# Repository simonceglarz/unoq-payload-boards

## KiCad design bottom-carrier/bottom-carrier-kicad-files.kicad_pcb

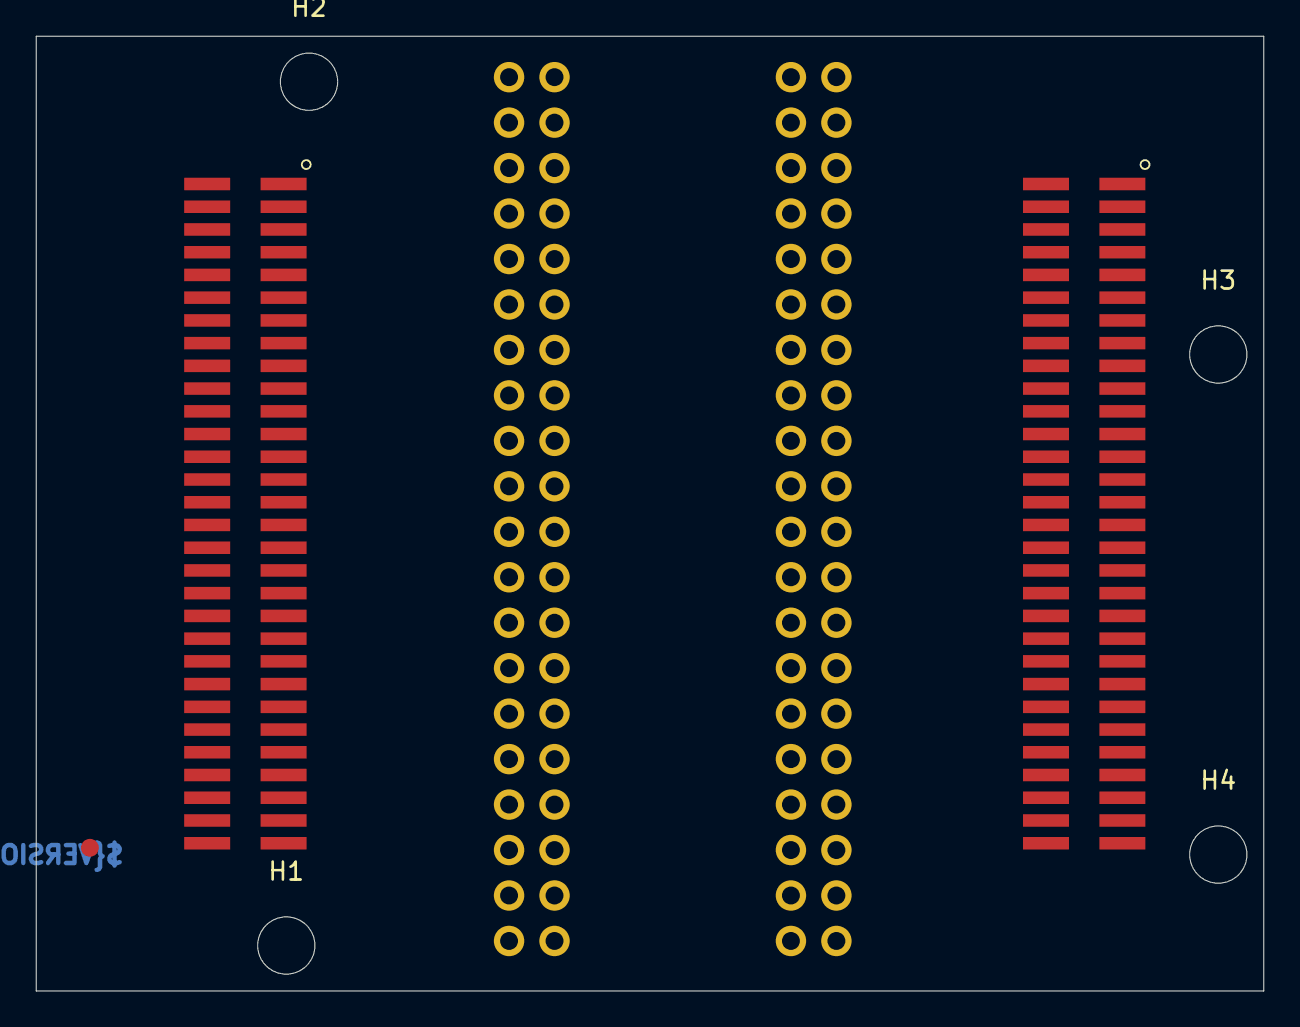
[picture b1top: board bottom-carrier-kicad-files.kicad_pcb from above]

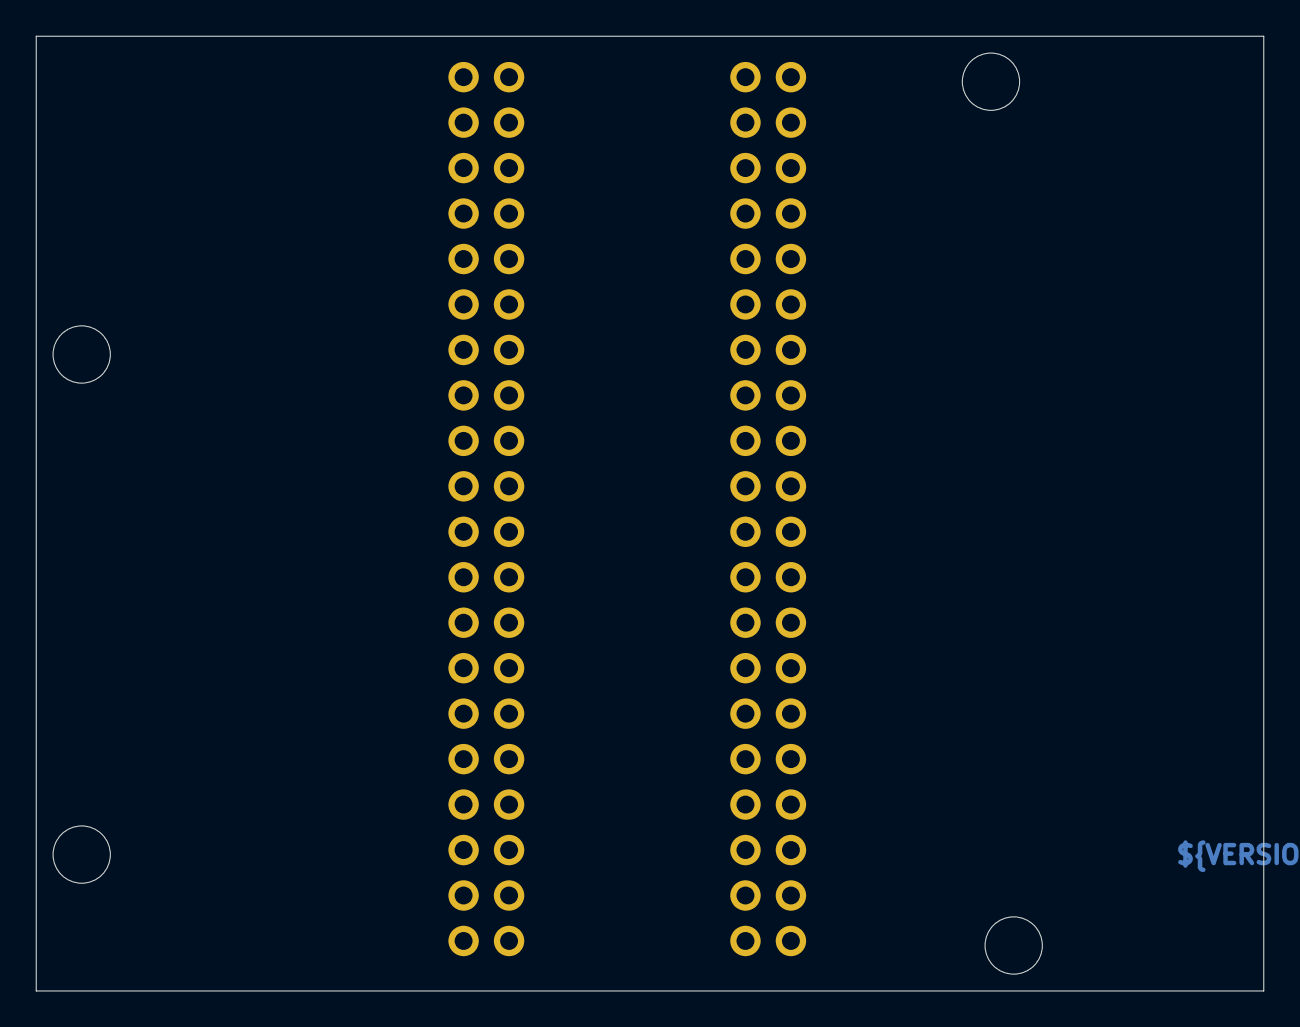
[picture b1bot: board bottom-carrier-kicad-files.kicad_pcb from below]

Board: 4 copper layers, 68.6 x 53.3 mm, 9 parts (2 on the bottom side), 61 nets, no tracks yet.

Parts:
Fiducial_2: Fiducial mark 1mm with 2mm solder; Fiducial mark 1mm with circle-Footprint-1
H1, H2, H3, H4: MountingHole_3.2mm_M3
J14, J15: PH2-40-UA; PIN HEADER 2.54mm VERT. 2x20POS
JMEDIA_MALE1: GPEC212-3002A011C1AF
JMISC_MALE1: GPEC212-3002A011C1AF

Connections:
+5V: J14.7, J14.9, JMISC_MALE1.54, JMISC_MALE1.56
DC_IN: J14.1, J14.3, JMEDIA_MALE1.57, JMEDIA_MALE1.59
GND: J14.5, J14.6, J14.11, J14.12, J14.17, J14.18, J14.23, J14.25, J14.26, J14.31, J14.32, J14.33, J14.37, J15.23, J15.30, J15.40, JMEDIA_MALE1.1, JMEDIA_MALE1.2, JMEDIA_MALE1.7, JMEDIA_MALE1.8, JMEDIA_MALE1.13, JMEDIA_MALE1.14, JMEDIA_MALE1.19, JMEDIA_MALE1.20, JMEDIA_MALE1.25, JMEDIA_MALE1.26, JMEDIA_MALE1.31, JMEDIA_MALE1.32, JMEDIA_MALE1.37, JMEDIA_MALE1.38, JMEDIA_MALE1.43, JMEDIA_MALE1.44, JMEDIA_MALE1.49, JMEDIA_MALE1.50, JMEDIA_MALE1.55, JMEDIA_MALE1.56, JMISC_MALE1.26, JMISC_MALE1.27, JMISC_MALE1.35, JMISC_MALE1.44, JMISC_MALE1.58
GPIO_22: J14.10, JMEDIA_MALE1.53
GPIO_23: J14.8, JMEDIA_MALE1.51
GPIO_29: J14.14, JMEDIA_MALE1.22
GPIO_30: J14.16, JMEDIA_MALE1.24
NetJ14_2: J14.2, JMEDIA_MALE1.16
NetJ14_4: J14.4, JMEDIA_MALE1.18
NetJ14_20: J14.20, JMISC_MALE1.29
NetJ14_22: J14.22, JMISC_MALE1.31
NetJ14_24: J14.24, JMISC_MALE1.33
NetJ14_27: J14.27, JMISC_MALE1.32
NetJ14_28: J14.28, JMISC_MALE1.28
NetJ14_29: J14.29, JMISC_MALE1.34
NetJ14_30: J14.30, JMISC_MALE1.30
NetJ14_34: J14.34, JMISC_MALE1.36
NetJ14_36: J14.36, JMISC_MALE1.38
NetJ14_38: J14.38, JMISC_MALE1.40
NetJ14_40: J14.40, JMISC_MALE1.42
NetJ15_1: J15.1, JMISC_MALE1.1
NetJ15_2: J15.2, JMISC_MALE1.2
NetJ15_3: J15.3, JMISC_MALE1.3
NetJ15_4: J15.4, JMISC_MALE1.4
NetJ15_5: J15.5, JMISC_MALE1.5
NetJ15_6: J15.6, JMISC_MALE1.6
NetJ15_7: J15.7, JMISC_MALE1.7
NetJ15_8: J15.8, JMISC_MALE1.8
NetJ15_9: J15.9, JMISC_MALE1.9
NetJ15_10: J15.10, JMISC_MALE1.10
NetJ15_11: J15.11, JMISC_MALE1.11
NetJ15_12: J15.12, JMISC_MALE1.12
NetJ15_13: J15.13, JMISC_MALE1.13
NetJ15_14: J15.14, JMISC_MALE1.14
NetJ15_15: J15.15, JMISC_MALE1.15
NetJ15_17: J15.17, JMISC_MALE1.17
NetJ15_19: J15.19, JMISC_MALE1.19
NetJ15_20: J15.20, JMISC_MALE1.20
NetJ15_21: J15.21, JMISC_MALE1.21
NetJ15_22: J15.22, JMISC_MALE1.22
NetJ15_24: J15.24, JMISC_MALE1.24
NetJ15_25: J15.25, JMISC_MALE1.37
NetJ15_26: J15.26, JMISC_MALE1.23
NetJ15_27: J15.27, JMISC_MALE1.39
NetJ15_28: J15.28, JMISC_MALE1.25
NetJ15_29: J15.29, JMISC_MALE1.41
NetJ15_31: J15.31, JMISC_MALE1.43
NetJ15_32: J15.32, JMISC_MALE1.46
NetJ15_33: J15.33, JMISC_MALE1.45
NetJ15_34: J15.34, JMISC_MALE1.48
NetJ15_35: J15.35, JMISC_MALE1.47
NetJ15_36: J15.36, JMISC_MALE1.50
NetJ15_37: J15.37, JMISC_MALE1.49
NetJ15_38: J15.38, JMISC_MALE1.52
NetJ15_39: J15.39, JMISC_MALE1.51
PF14: J15.16, JMISC_MALE1.16
PF15: J15.18, JMISC_MALE1.18
PWR_3P3V: J14.13, J14.15, JMEDIA_MALE1.58, JMEDIA_MALE1.60, JMISC_MALE1.53, JMISC_MALE1.55
VBAT: J14.35, JMISC_MALE1.60
VCC_PX3_1P8: J14.19, J14.21, JMISC_MALE1.57
VCOIN: J14.39, JMISC_MALE1.59

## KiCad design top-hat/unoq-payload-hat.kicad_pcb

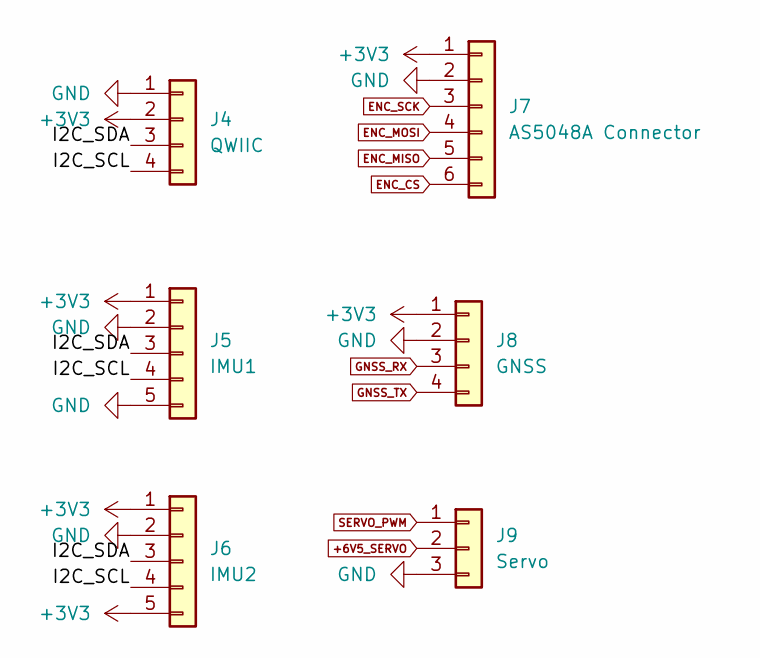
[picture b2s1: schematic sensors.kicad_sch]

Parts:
J4: QWIIC; PinHeader_1x04_P2.54mm_Vertical
J5: IMU1; PinHeader_1x05_P2.54mm_Vertical
J6: IMU2; PinHeader_1x05_P2.54mm_Vertical
J7: AS5048A Connector; PinHeader_1x06_P2.54mm_Vertical
J8: GNSS; PinHeader_1x04_P2.54mm_Vertical
J9: Servo; PinHeader_1x03_P2.54mm_Vertical

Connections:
+3V3: J4.2, J5.1, J6.1, J6.5, J7.1, J8.1; also elsewhere on the board
+6V5_SERVO: J9.2
/sensors/I2C_SCL: J4.4, J5.4, J6.4
/sensors/I2C_SDA: J4.3, J5.3, J6.3
ENC_CS: J7.6; also elsewhere on the board
ENC_MISO: J7.5; also elsewhere on the board
ENC_MOSI: J7.4; also elsewhere on the board
ENC_SCK: J7.3; also elsewhere on the board
GND: J4.1, J5.2, J5.5, J6.2, J7.2, J8.2, J9.3; also elsewhere on the board
GNSS_RX: J8.3; also elsewhere on the board
GNSS_TX: J8.4; also elsewhere on the board
SERVO_PWM: J9.1; also elsewhere on the board

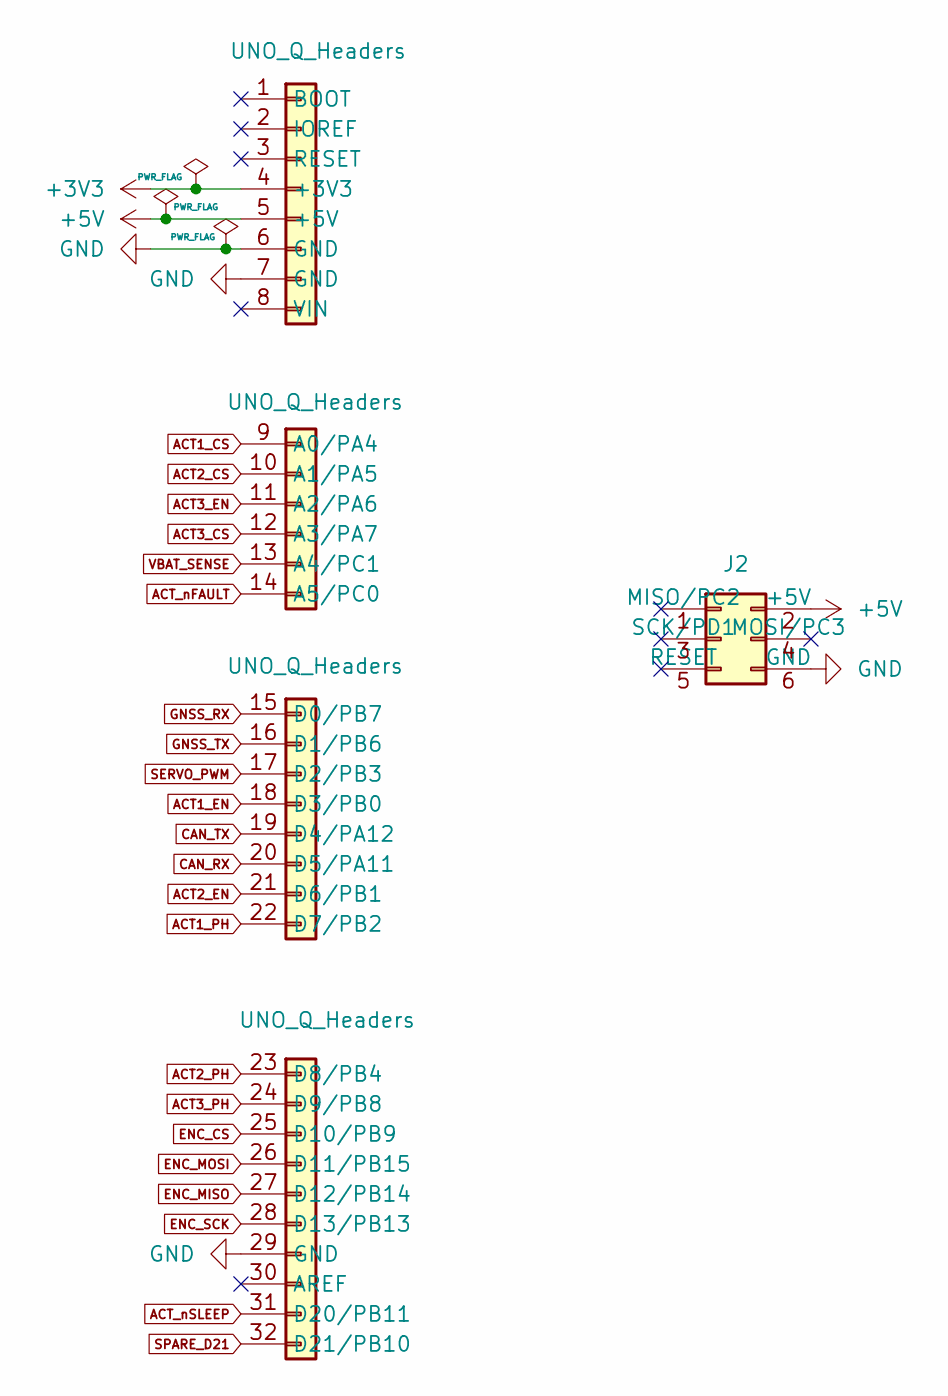
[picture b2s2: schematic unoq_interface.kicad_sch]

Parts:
J1: UNO_Q_Headers; Arduino_UNO_R3
J2: PinHeader_2x03_P2.54mm_Vertical

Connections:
+3V3: J1.4 (+3V3); also elsewhere on the board
+5V: J1.5 (+5V), J2.2 (+5V); also elsewhere on the board
ACT1_CS: J1.9 (A0/PA4)
ACT1_EN: J1.18 (D3/PB0)
ACT1_PH: J1.22 (D7/PB2)
ACT2_CS: J1.10 (A1/PA5)
ACT2_EN: J1.21 (D6/PB1)
ACT2_PH: J1.23 (D8/PB4)
ACT3_CS: J1.12 (A3/PA7)
ACT3_EN: J1.11 (A2/PA6)
ACT3_PH: J1.24 (D9/PB8)
ACT_nFAULT: J1.14 (A5/PC0)
ACT_nSLEEP: J1.31 (D20/PB11)
CAN_RX: J1.20 (D5/PA11); also elsewhere on the board
CAN_TX: J1.19 (D4/PA12); also elsewhere on the board
ENC_CS: J1.25 (D10/PB9); also elsewhere on the board
ENC_MISO: J1.27 (D12/PB14); also elsewhere on the board
ENC_MOSI: J1.26 (D11/PB15); also elsewhere on the board
ENC_SCK: J1.28 (D13/PB13); also elsewhere on the board
GND: J1.6 (GND), J1.7 (GND), J1.29 (GND), J2.6 (GND); also elsewhere on the board
GNSS_RX: J1.15 (D0/PB7); also elsewhere on the board
GNSS_TX: J1.16 (D1/PB6); also elsewhere on the board
SERVO_PWM: J1.17 (D2/PB3); also elsewhere on the board
SPARE_D21: J1.32 (D21/PB10)
VBAT_SENSE: J1.13 (A4/PC1)

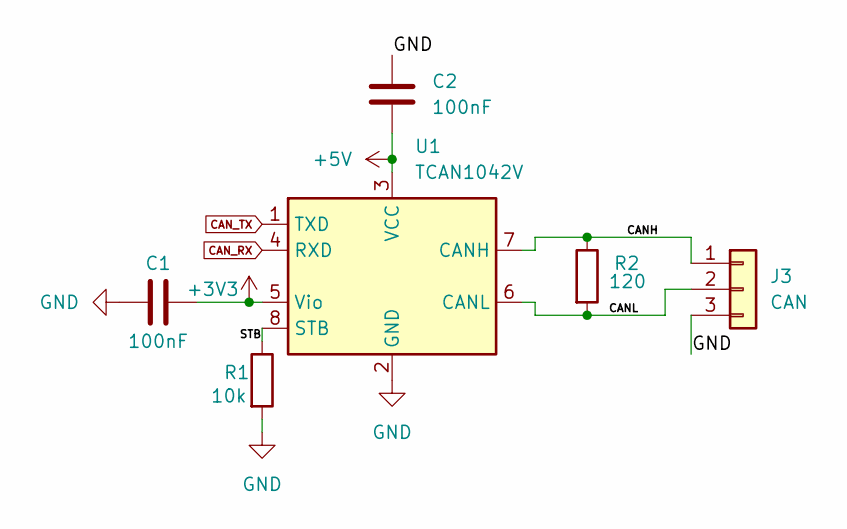
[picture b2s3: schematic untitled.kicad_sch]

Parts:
C1, C2: 100nF; C_1206_3216Metric
J3: CAN; PinHeader_1x03_P2.54mm_Vertical
R1: 10k; R_1206_3216Metric
R2: 120; R_1206_3216Metric
U1: TCAN1042V; SOIC-8_3.9x4.9mm_P1.27mm

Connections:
+3V3: C1.2, U1.5 (Vio); also elsewhere on the board
+5V: C2.1, U1.3 (VCC); also elsewhere on the board
/can/CANH: J3.1, R2.1, U1.7 (CANH)
/can/CANL: J3.2, R2.2, U1.6 (CANL)
/can/STB: R1.1, U1.8 (STB)
CAN_RX: U1.4 (RXD); also elsewhere on the board
CAN_TX: U1.1 (TXD); also elsewhere on the board
GND: C1.1, C2.2, J3.3, R1.2, U1.2 (GND); also elsewhere on the board

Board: 2 copper layers, 14 parts (0 on the bottom side), 17 nets, no tracks yet.
